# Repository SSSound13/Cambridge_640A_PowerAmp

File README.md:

# Новая плата для любимого Cambridge 640A

> [!CAUTION]
> Версия сейчас находится на проверке.

Cambridge Audio Azur 640A хочется сохранить в работе. Этот проект посвящён восстановлению усилителя на новой четырёхслойной плате: с привычной схемотехникой, выходными модулями Sanken SAP15 и более удобным обслуживанием.

Плата разработана для **640A первой версии (V1)** на основе заводского узла AP12707/6 и PCB AP12708/6a. Можно использовать пригодные детали исходного усилителя, а схему, разводку и каждое изменение изучить в KiCad.

*Монтажный вид из KiCad, не фотография собранной платы. [Рассмотреть в деталях](doc/v2/preview/front-assembly.png).*

## Что даёт новая плата

### Сохранить знакомый усилитель

В основе остаётся схема Cambridge, включая выходные SAP15. Контур и крепёж взяты за основу из оригинальной конструкции, чтобы проект подходил для восстановления имеющегося аппарата. Перенос исправных компонентов позволяет сохранить значительную часть усилителя. При этом SAP15 сняты с производства, а фактическую посадку деталей и радиатора ещё нужно проверить.

### Меньше проводов, проще обслуживание

Соединения, которые раньше выполнялись перемычками и проводами, перенесены в медь четырёхслойной платы. Трансформатор и акустика подключаются через разъёмы JST: для снятия платы эти провода больше не нужно отпаивать. Отдельные контрольные точки облегчают подключение щупов при настройке тока покоя, а крупные подписи помогают ориентироваться при сборке.

### Свой путь для силовых и сигнальных токов

Выходной каскад потребляет большие токи, а вход работает с малым сигналом. Если они используют общие участки земли, падение напряжения на этих участках может влиять на сигнал.

В новой разводке силовая, сигнальная, цифровая и вспомогательная земли разделены и сведены к звезде. Внутренние слои используются для питания и силовой земли. Цель: уменьшить взаимное влияние цепей и сделать пути токов понятными. Реальный результат по шуму и устойчивости предстоит измерить.

### Изменения с понятной причиной

В питании входных каскадов применены огнестойкие резисторы большей мощности, в основном выпрямителе выбраны диоды с большим запасом по току. Добавлены резисторы, ограничивающие рост сопротивления цепи регулировки тока покоя, и RC-снабберы для подавления звона вторичной обмотки.

На входе используются плёночные конденсаторы, увеличена ёмкость конденсаторов обратной связи. У каждой замены есть конкретная задача. Итоговую АЧХ, нагрев и поведение при неисправностях ещё нужно проверить; обещаний улучшенного звука без измерений здесь нет.

### Исходники, которые можно изучить и доработать

Схема, плата, специальные библиотеки и перечень компонентов доступны в репозитории. Можно проследить соединения, подобрать детали и понять причины изменений. В BOM указаны партномера и замечания по монтажу, рядом сохранены изображения и результаты проверок. Проект полезен и для собственного ремонта, и для обсуждения решений с другими разработчиками.

## Сравнение с оригиналом

Что меняется при переходе с заводской платы на новую. Номиналы и конструкция относятся к **актуальным исходникам v2**, а не старому производственному архиву. Три строки с отметкой ¹ содержат прежние расчётные оценки, ещё не перепроверенные для текущей v2. Результаты работы собранного усилителя предстоит измерить.

| Параметр | Оригинал AP12708/6a | Новая плата v2 |
|---|---|---|
| Слои меди | Один снизу, соединения сверху перемычками | Четыре; в проекте 70 мкм снаружи и 35 мкм внутри, номинальная толщина платы 1,6 мм |
| Перемычки | 19 LK по схеме и 5 проволочных WIRE LINK | Соединения выполнены медью платы; впаивать перемычки не нужно |
| Провода трансформатора и акустики | Впаяны в клеммы | Разъёмы JST VH 3,96 мм для силовых цепей и XH 2,5 мм для вспомогательной обмотки; J4 для корпуса сохранена |
| Питание ±45 В выходных каскадов | Дорожки и отрезки провода | Полигоны In1.Cu, шины батареи конденсаторов шириной 3,4 мм |
| Силовая земля | Дорожки и провода WIRE1–4 к звезде | Полигон PGND на отдельном внутреннем слое In2.Cu |
| Разделение земель | Провода и общие участки дорожек | PGND / GND / digital / AUX0V, соединение в звезде NT1–NT3 |
| Влияние токов фильтров на опору входа, мВ/А (L / R)¹ | 11,5 / 21,8 | 0,15 / 0,15 |
| Влияние тока заряда и выпрямителя на опору входа, мВ/А¹ | 0,03–0,05 | 0 в прежней модели |
| Перекрёстная связь возвратов АС L↔R, мВ/А¹ | 0,008 | 0,0002 |
| Мост основного питания D17–D20 | 1N5402, 3 А | Diotec BY550-400, 5 А / 400 В, по текущему BOM |
| Снабберы вторичной обмотки | Нет | 47 Ом + 100 нФ на каждую половину; сопротивление подбирается по измеренному звону |
| Регулировка тока покоя R116 / R68 | Реостат 47 Ом | Добавлены параллельные 100 Ом R120 / R121; исправная цепь до ≈32 Ом² |
| Контроль тока покоя | Щупы на выводах резисторов 0,22 Ом | Отдельные контрольные точки TP1–TP6 |
| R41, R43, R96, R98 | 150 Ом / 0,25 Вт | 150 Ом / 0,5 Вт, огнестойкие |
| Входной конденсатор C18 / C39 | 10 мкФ, неполярный электролит | 2,2 мкФ, плёнка WIMA MKS2 |
| Конденсатор обратной связи C17 / C41 | 100 мкФ NP; расчётный полюс RC ≈1,6 Гц³ | 220 мкФ NP; расчётный полюс RC ≈0,7 Гц³ |
| Цепь Цобеля C24 / C28 | 100 нФ и 4,7 Ом / 3 Вт | 100 нФ / 250 В MKT; резисторы 4,7 Ом / 3 Вт остаются проволочными |
| +5 В для PIC | 7805 на общем радиаторе с 7815 / 7915 | Возвращён штатный 7805 на общем радиаторе, стандартный KiCad TO-220; TRACO не используется, C81 удалён |
| Электрическая связь радиатора стабилизаторов | Через фланец 7805 | Через фланец U8 (digital); отдельная дорожка H8 удалена. U9 и U10 устанавливаются с изоляторами |
| Выходные модули | Sanken SAP15N / SAP15P | Те же типы модулей, монтаж на радиаторе; фактическая посадка проверяется при сборке |
| Топология усилителя и защиты | Схемотехника Cambridge 640A V1 | Базовая схема сохранена; доработаны вспомогательные цепи, компоненты и разводка |

¹ **Исторические расчётные оценки, не результаты измерений.** Эти три строки восстановлены из [прежнего сравнения и расчёта сопротивлений земли от 25.09.2026](https://github.com/SSSound13/Cambridge_640A_PowerAmp/blob/8188b4cc4bade1c1e03b41d10146da4cc2be14a8/README.md). Расчёт не повторён для текущей исправленной v2. Ноль в резистивной модели не означает отсутствия реальных помех, а эти числа не являются измерением шума или разделения каналов усилителя.

² 47 Ом ∥ 100 Ом ≈ 32 Ом по номиналам компонентов. Это не гарантия безопасного тока покоя при любой неисправности; поведение требует проверки.

³ Оценка отдельной RC-цепи при 1 кОм: 1 / (2πRC). Это не измеренная нижняя граница АЧХ всего усилителя.

Полные типы деталей и монтажные ограничения: [BOM](BOM.md). Текущие исправления и проверки: [описание v2](doc/v2/MINIMAL_FIXES.md) и [результаты проверок](doc/v2/VALIDATION.md).

## Версия 2: что уже сделано и что дальше

После первой изготовленной партии подготовлены минимальные исправления v2:

- Устранено ошибочное соединение входа U6 с +15 V.
- Возвращён стабилизатор 7805, убраны C81 и отдельная дорожка H8 для установки целого радиатора.
- Укрупнены и упорядочены подписи, добавлены обозначения контрольных точек, контур радиатора и ссылка на проект. QR расположен сверху под H2, над R71; полный URL текстом сохранён снизу.

Остальные компоненты сохранены на своих местах. Проверки файлов выполнены, но работа собранной платы, защита, механика и тепловой режим ещё не подтверждены. Подробности: [исправления и монтаж](doc/v2/MINIMAL_FIXES.md), [результаты и границы проверок](doc/v2/VALIDATION.md).

**Gerber обновлены 07.11.2026:** [текущий комплект](gerber/) и [ZIP](640A_PowerAmp_v2_fab_2026-11-07.zip) обновлены после смещения R12 на 0,8 мм вниз от C7; четыре остальных пересечения приняты в исключения. Исправление U6 сохранено. Проверка: 0 ошибок, 0 активных предупреждений, 0 неразведённых соединений и расхождений со схемой. [Состав, настройки и результаты проверки](gerber/README.md). **ZIP от 03.10.2026 остаётся только историческим архивом: в нём ошибочная связь U6 с +15 V, использовать его для нового заказа нельзя.** Обновление файлов не исправляет уже изготовленную плату.

В [отдельном плане v3](https://github.com/SSSound13/Cambridge_640A_PowerAmp/blob/v3/TODO.md) находятся симметричная компоновка каналов и дальнейшее улучшение размещения компонентов.

## С чего начать

- **Посмотреть плату:** [монтажный вид и шелкография](doc/v2/preview/).
- **Разобраться с деталями:** [BOM и замечания по сборке](BOM.md).
- **Открыть исходники:** [проект KiCad](640A_PowerAmp.kicad_pro), нужен KiCad 10.0 или новее.
- **Проверить текущий статус:** [исправления v2](doc/v2/MINIMAL_FIXES.md) и [проверки](doc/v2/VALIDATION.md). Старые отчёты и сборочные PDF оставлены для истории.

Здесь **V1 означает поколение усилителя**, а **v2 означает версию новой платы**. Совместимость с Cambridge 640A V2 не заявляется.

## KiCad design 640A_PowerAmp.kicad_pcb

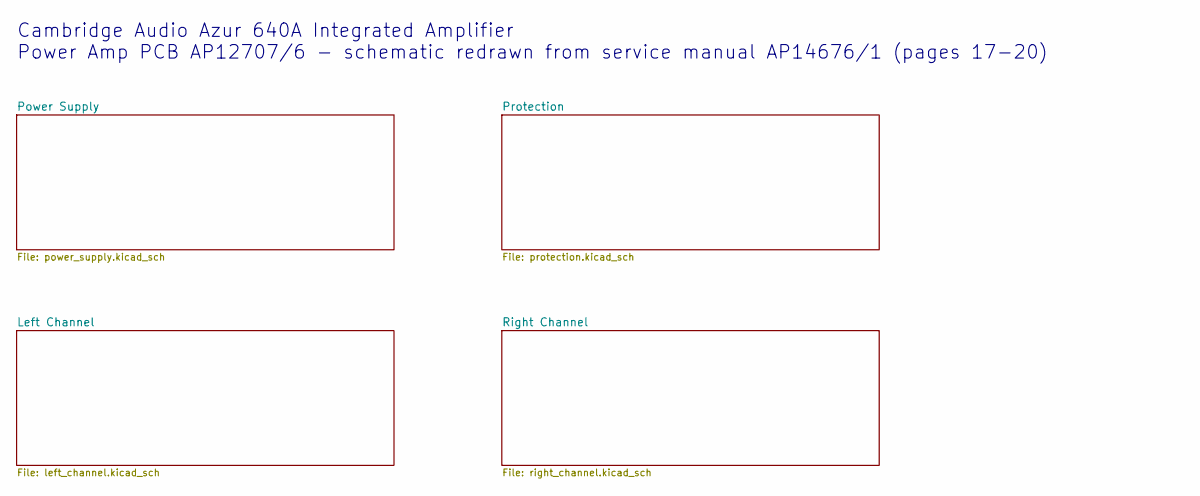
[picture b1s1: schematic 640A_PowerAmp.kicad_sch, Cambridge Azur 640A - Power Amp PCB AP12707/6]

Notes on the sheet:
Cambridge Audio Azur 640A Integrated Amplifier Power Amp PCB AP12707/6 - schematic redrawn from service manual AP14676/1 (pages 17-20)

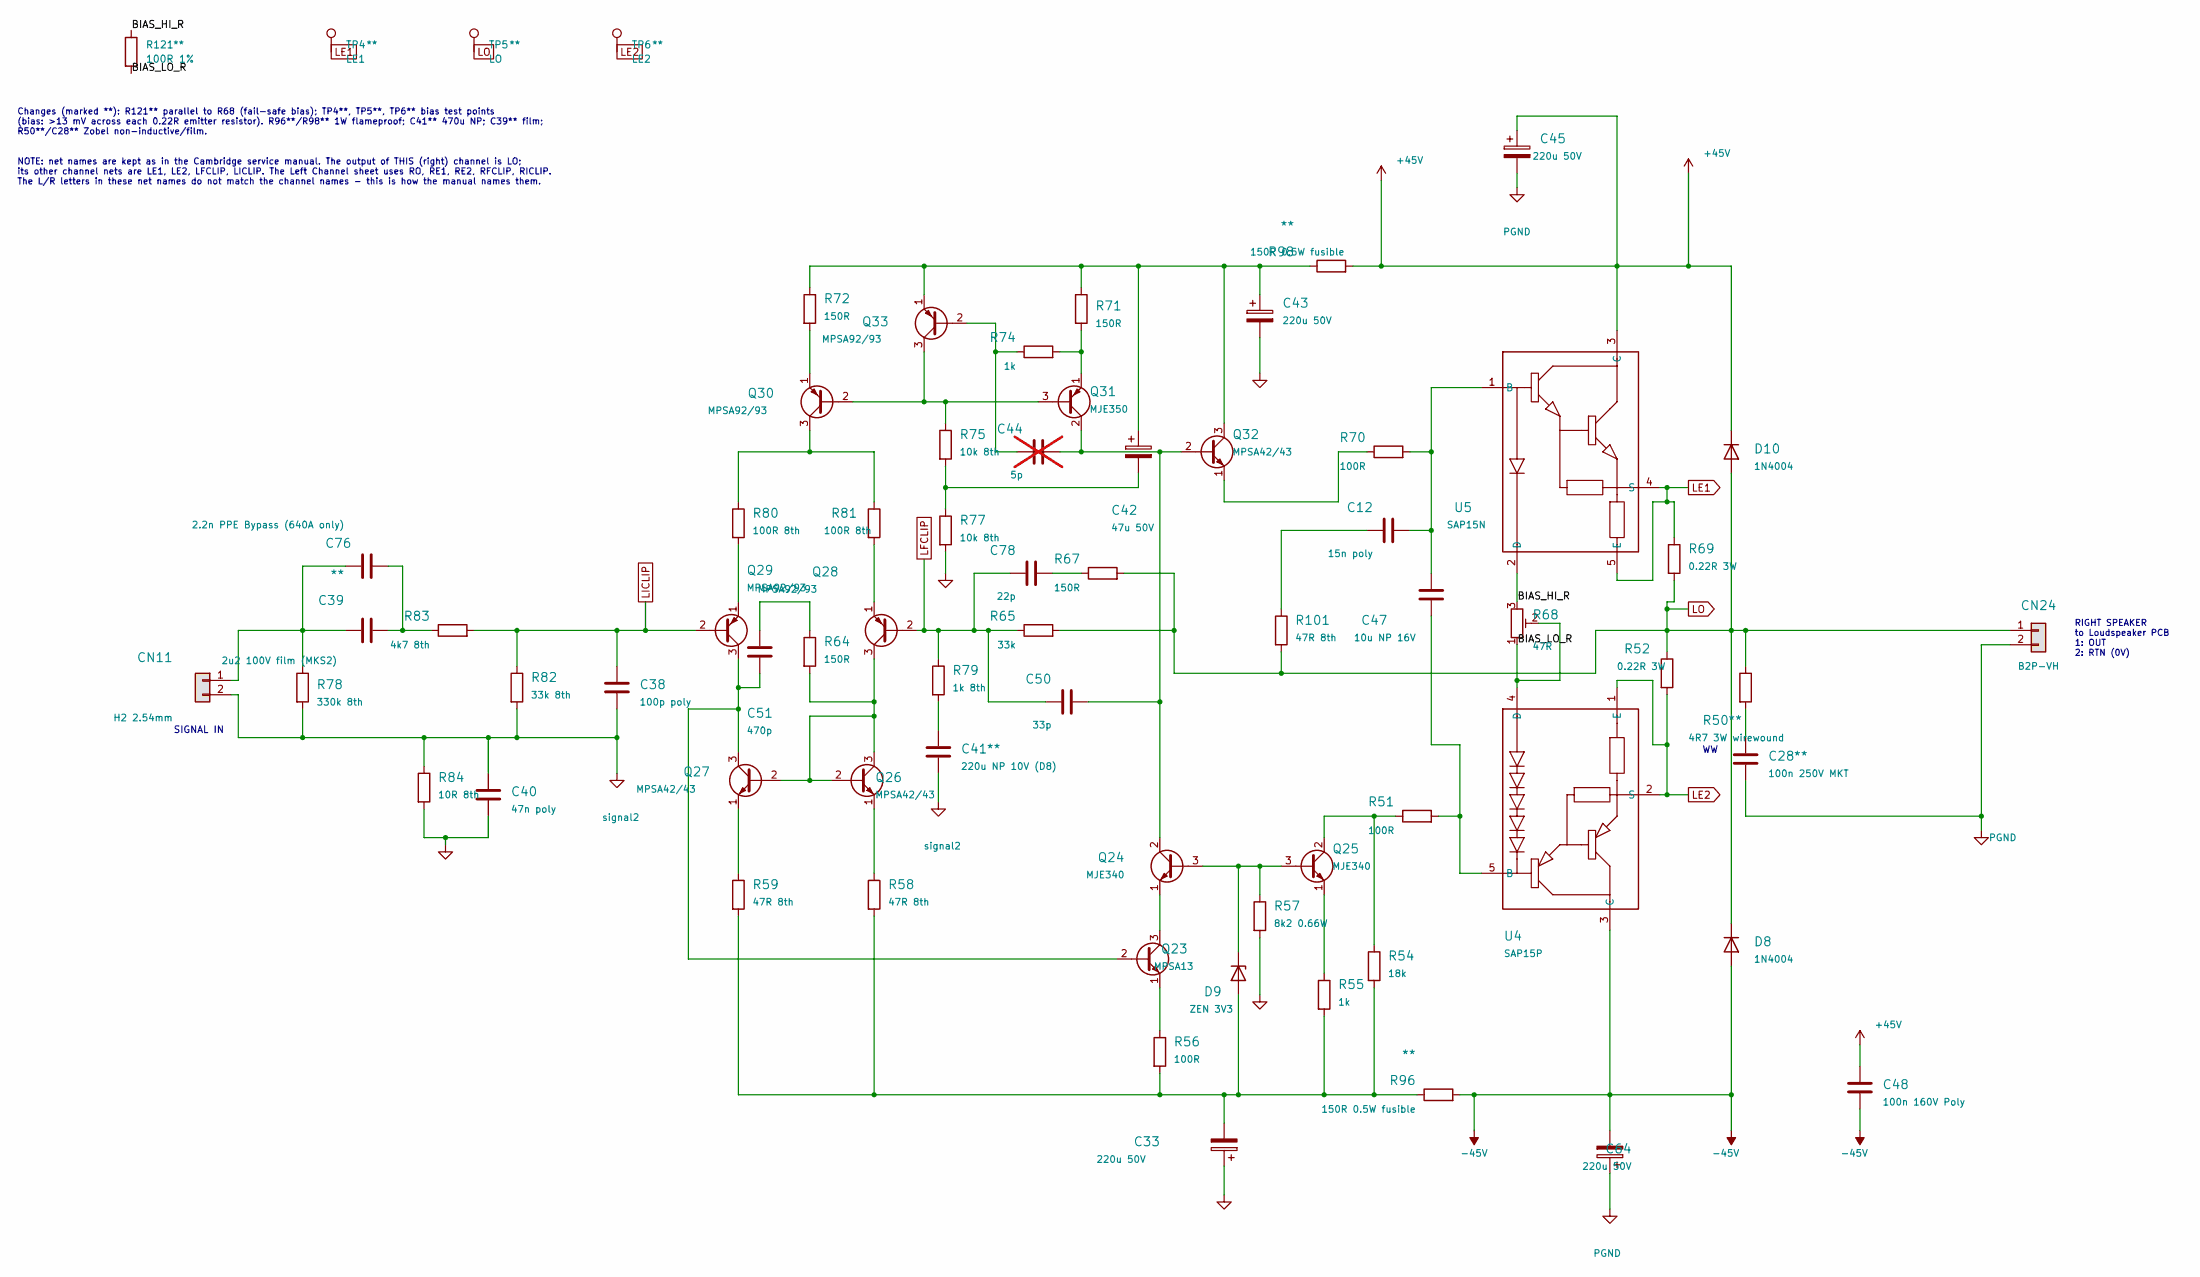
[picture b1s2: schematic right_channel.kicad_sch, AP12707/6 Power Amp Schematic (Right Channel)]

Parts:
C12: 15n poly; C_Rect_L7.2mm_W2.5mm_P5.00mm_FKS2_FKP2_MKS2_MKP2
C28: 100n 250V MKT; C_Rect_L9.0mm_W3.2mm_P7.50mm_MKT; MPN B32560J3104K000
C33, C43, C45, C64: 220u 50V; CP_Radial_D10.0mm_P5.00mm
C38: 100p poly; C_Rect_L7.2mm_W2.5mm_P5.00mm_FKS2_FKP2_MKS2_MKP2
C39: 2u2 100V film (MKS2); C_Rect_L7.2mm_W11.0mm_P5.00mm_FKS2_FKP2_MKS2_MKP2; MPN MKS2D042201N00KO00 (MKS2-2.2U/100-R)
C40: 47n poly; C_Rect_L7.2mm_W2.5mm_P5.00mm_FKS2_FKP2_MKS2_MKP2
C41: 220u NP 10V (D8); C_Radial_D8.0mm_H11.5mm_P3.50mm; MPN ECE-A1AN221U
C42: 47u 50V; CP_Radial_D6.3mm_P2.50mm
C44: 5p; C_Disc_D5.0mm_W2.5mm_P5.00mm; not fitted
C47: 10u NP 16V; C_Radial_D5.0mm_P5.00mm_NP
C48: 100n 160V Poly; C_Rect_L13.0mm_W4.0mm_P10.00mm_FKS3_FKP3_MKS4
C50: 33p; C_Rect_L7.2mm_W2.5mm_P5.00mm_FKS2_FKP2_MKS2_MKP2
C51: 470p; C_Disc_D5.0mm_W2.5mm_P5.00mm
C76: 2.2n PPE Bypass (640A only); C_Rect_L7.2mm_W2.5mm_P5.00mm_FKS2_FKP2_MKS2_MKP2
C78: 22p; C_Disc_D5.0mm_W2.5mm_P5.00mm
CN11: H2 2.54mm; JST_XH_B2B-XH-A_1x02_P2.50mm_Vertical
CN24: B2P-VH; JST_VH_B2P-VH_1x02_P3.96mm_Vertical; MPN B2P-VH
D8, D10: 1N4004; D_DO-41_SOD81_P8.89mm_Horizontal
D9: ZEN 3V3; D_DO-35_SOD27_P7.62mm_Horizontal
Q23: MPSA13; TO-92_Inline_Wide
Q24, Q25: MJE340; TO-126-3_Vertical
Q26, Q27, Q32: MPSA42/43; TO-92_Inline_Wide
Q28, Q29, Q30, Q33: MPSA92/93; TO-92_Inline_Wide
Q31: MJE350; TO-126-3_Vertical
R50: 4R7 3W wirewound; R_Axial_DIN0516_L15.5mm_D5.0mm_P18.42mm_Horizontal; MPN AC03000004708JAC00
R51, R56, R70: 100R; R_Axial_DIN0207_L6.3mm_D2.5mm_P10.16mm_Horizontal
R52, R69: 0.22R 3W; R_Axial_DIN0516_L15.5mm_D5.0mm_P19.69mm_Horizontal
R54: 18k; R_Axial_DIN0207_L6.3mm_D2.5mm_P10.16mm_Horizontal
R55, R74: 1k; R_Axial_DIN0207_L6.3mm_D2.5mm_P10.16mm_Horizontal
R57: 8k2 0.66W; R_Axial_DIN0309_L9.0mm_D3.2mm_P11.81mm_Horizontal
R58, R59: 47R 8th; R_Axial_DIN0204_L3.6mm_D1.6mm_P7.62mm_Horizontal
R64, R67: 150R; R_Axial_DIN0204_L3.6mm_D1.6mm_P7.62mm_Horizontal
R65: 33k; R_Axial_DIN0207_L6.3mm_D2.5mm_P10.16mm_Horizontal
R68: 47R; Potentiometer_Bourns_3296W_Vertical
R71, R72: 150R; R_Axial_DIN0207_L6.3mm_D2.5mm_P10.16mm_Horizontal
R75, R77: 10k 8th; R_Axial_DIN0204_L3.6mm_D1.6mm_P7.62mm_Horizontal
R78: 330k 8th; R_Axial_DIN0204_L3.6mm_D1.6mm_P7.62mm_Horizontal
R79: 1k 8th; R_Axial_DIN0204_L3.6mm_D1.6mm_P7.62mm_Horizontal
R80, R81: 100R 8th; R_Axial_DIN0204_L3.6mm_D1.6mm_P7.62mm_Horizontal
R82: 33k 8th; R_Axial_DIN0204_L3.6mm_D1.6mm_P7.62mm_Horizontal
R83: 4k7 8th; R_Axial_DIN0204_L3.6mm_D1.6mm_P7.62mm_Horizontal
R84: 10R 8th; R_Axial_DIN0204_L3.6mm_D1.6mm_P7.62mm_Horizontal
R96, R98: 150R 0.5W fusible; R_Axial_DIN0207_L6.3mm_D2.5mm_P10.16mm_Horizontal; MPN FRN50J150R/S
R101: 47R 8th; R_Axial_DIN0204_L3.6mm_D1.6mm_P5.08mm_Horizontal
R121: 100R 1%; R_Axial_DIN0204_L3.6mm_D1.6mm_P2.54mm_Vertical; MPN MF-25 0.25W 100R 1%
TP4: LE1; TestPoint_THTPad_D2.0mm_Drill1.0mm
TP5: LO; TestPoint_THTPad_D2.0mm_Drill1.0mm
TP6: LE2; TestPoint_THTPad_D2.0mm_Drill1.0mm
U4: SAP15P; TO-3P-5_SAP15_Horizontal
U5: SAP15N; TO-3P-5_SAP15_Horizontal

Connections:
+45V: C45.1, C48.1, D10.1 (K), R98.2, U5.3 (C); also elsewhere on the board
-45V: C48.2, C64.2, D8.2 (A), R96.2, U4.3 (C); also elsewhere on the board
/Right Channel/BIAS_HI_R: R68.3, R121.1, U5.2 (D)
/Right Channel/BIAS_LO_R: R68.1, R68.2, R121.2, U4.4 (D)
GND: C33.1, C40.2, C43.2, R57.2, R77.2, R84.2; also elsewhere on the board
LE1: R69.1, TP4.1 (1_1), U5.4 (S), U5.5 (E); also elsewhere on the board
LE2: R52.2, TP6.1 (1_1), U4.1 (E), U4.2 (S); also elsewhere on the board
LFCLIP: C50.1, C78.1, Q28.2 (B), R65.1, R79.1; also elsewhere on the board
LICLIP: C38.1, Q29.2 (B), R82.1, R83.2; also elsewhere on the board
LO: CN24.1, D8.1 (K), D10.2 (A), R50.1, R52.1, R65.2, R67.2, R69.2, R101.2, TP5.1 (1_1); also elsewhere on the board
unnamed: C12.1, R101.1
unnamed: C28.1, R50.2
unnamed: C39.2, C76.2, R83.1
unnamed: C41.1, R79.2
unnamed: C42.2, R75.2, R77.1
unnamed: C51.1, R64.1
unnamed: C78.2, R67.1
unnamed: C39.1, C76.1, CN11.1, R78.1
unnamed: C33.2, D9.2 (A), R54.2, R55.2, R56.2, R58.2, R59.2, R96.1
unnamed: D9.1 (K), Q24.3 (B), Q25.3 (B), R57.1
unnamed: C51.2, Q23.2 (B), Q27.3 (C), Q29.3 (C)
unnamed: Q23.3 (C), Q24.1 (E)
unnamed: Q23.1 (E), R56.1
unnamed: C44.2, C50.2, Q24.2 (C), Q31.2 (C), Q32.2 (B)
unnamed: Q25.2 (C), R51.1, R54.1
unnamed: Q25.1 (E), R55.1
unnamed: Q26.2 (B), Q26.3 (C), Q27.2 (B), Q28.3 (C), R64.2
unnamed: Q26.1 (E), R58.1
unnamed: Q27.1 (E), R59.1
unnamed: Q28.1 (E), R81.2
unnamed: Q29.1 (E), R80.2
unnamed: Q30.2 (B), Q31.3 (B), Q33.3 (C), R75.1
unnamed: Q30.3 (C), R80.1, R81.1
unnamed: Q30.1 (E), R72.2
unnamed: Q31.1 (E), R71.2, R74.2
unnamed: C42.1, C43.1, Q32.3 (C), Q33.1 (E), R71.1, R72.1, R98.1
unnamed: Q32.1 (E), R70.1
unnamed: C44.1, Q33.2 (B), R74.1
unnamed: C47.2, R51.2, U4.5 (B)
unnamed: C12.2, C47.1, R70.2, U5.1 (B)
PGND: C28.2, C45.2, C64.1, CN24.2; also elsewhere on the board
signal2: C38.2, C40.1, C41.2, CN11.2, R78.2, R82.2, R84.1

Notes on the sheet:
RIGHT SPEAKER to Loudspeaker PCB 1: OUT 2: RTN (0V)
NOTE: net names are kept as in the Cambridge service manual. The output of THIS (right) channel is LO; its other channel nets are LE1, LE2, LFCLIP, LICLIP. The Left Channel sheet uses RO, RE1, RE2, RFCLIP, RICLIP. The L/R letters in these net names do not match the channel names - this is how the m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
SIGNAL IN
Changes (marked **): R121** parallel to R68 (fail-safe bias); TP4**, TP5**, TP6** bias test points (bias: >13 mV across each 0.22R emitter resistor). R96**/R98** 1W flameproof; C41** 470u NP; C39** film; R50**/C28** Zobel non-inductive/film.

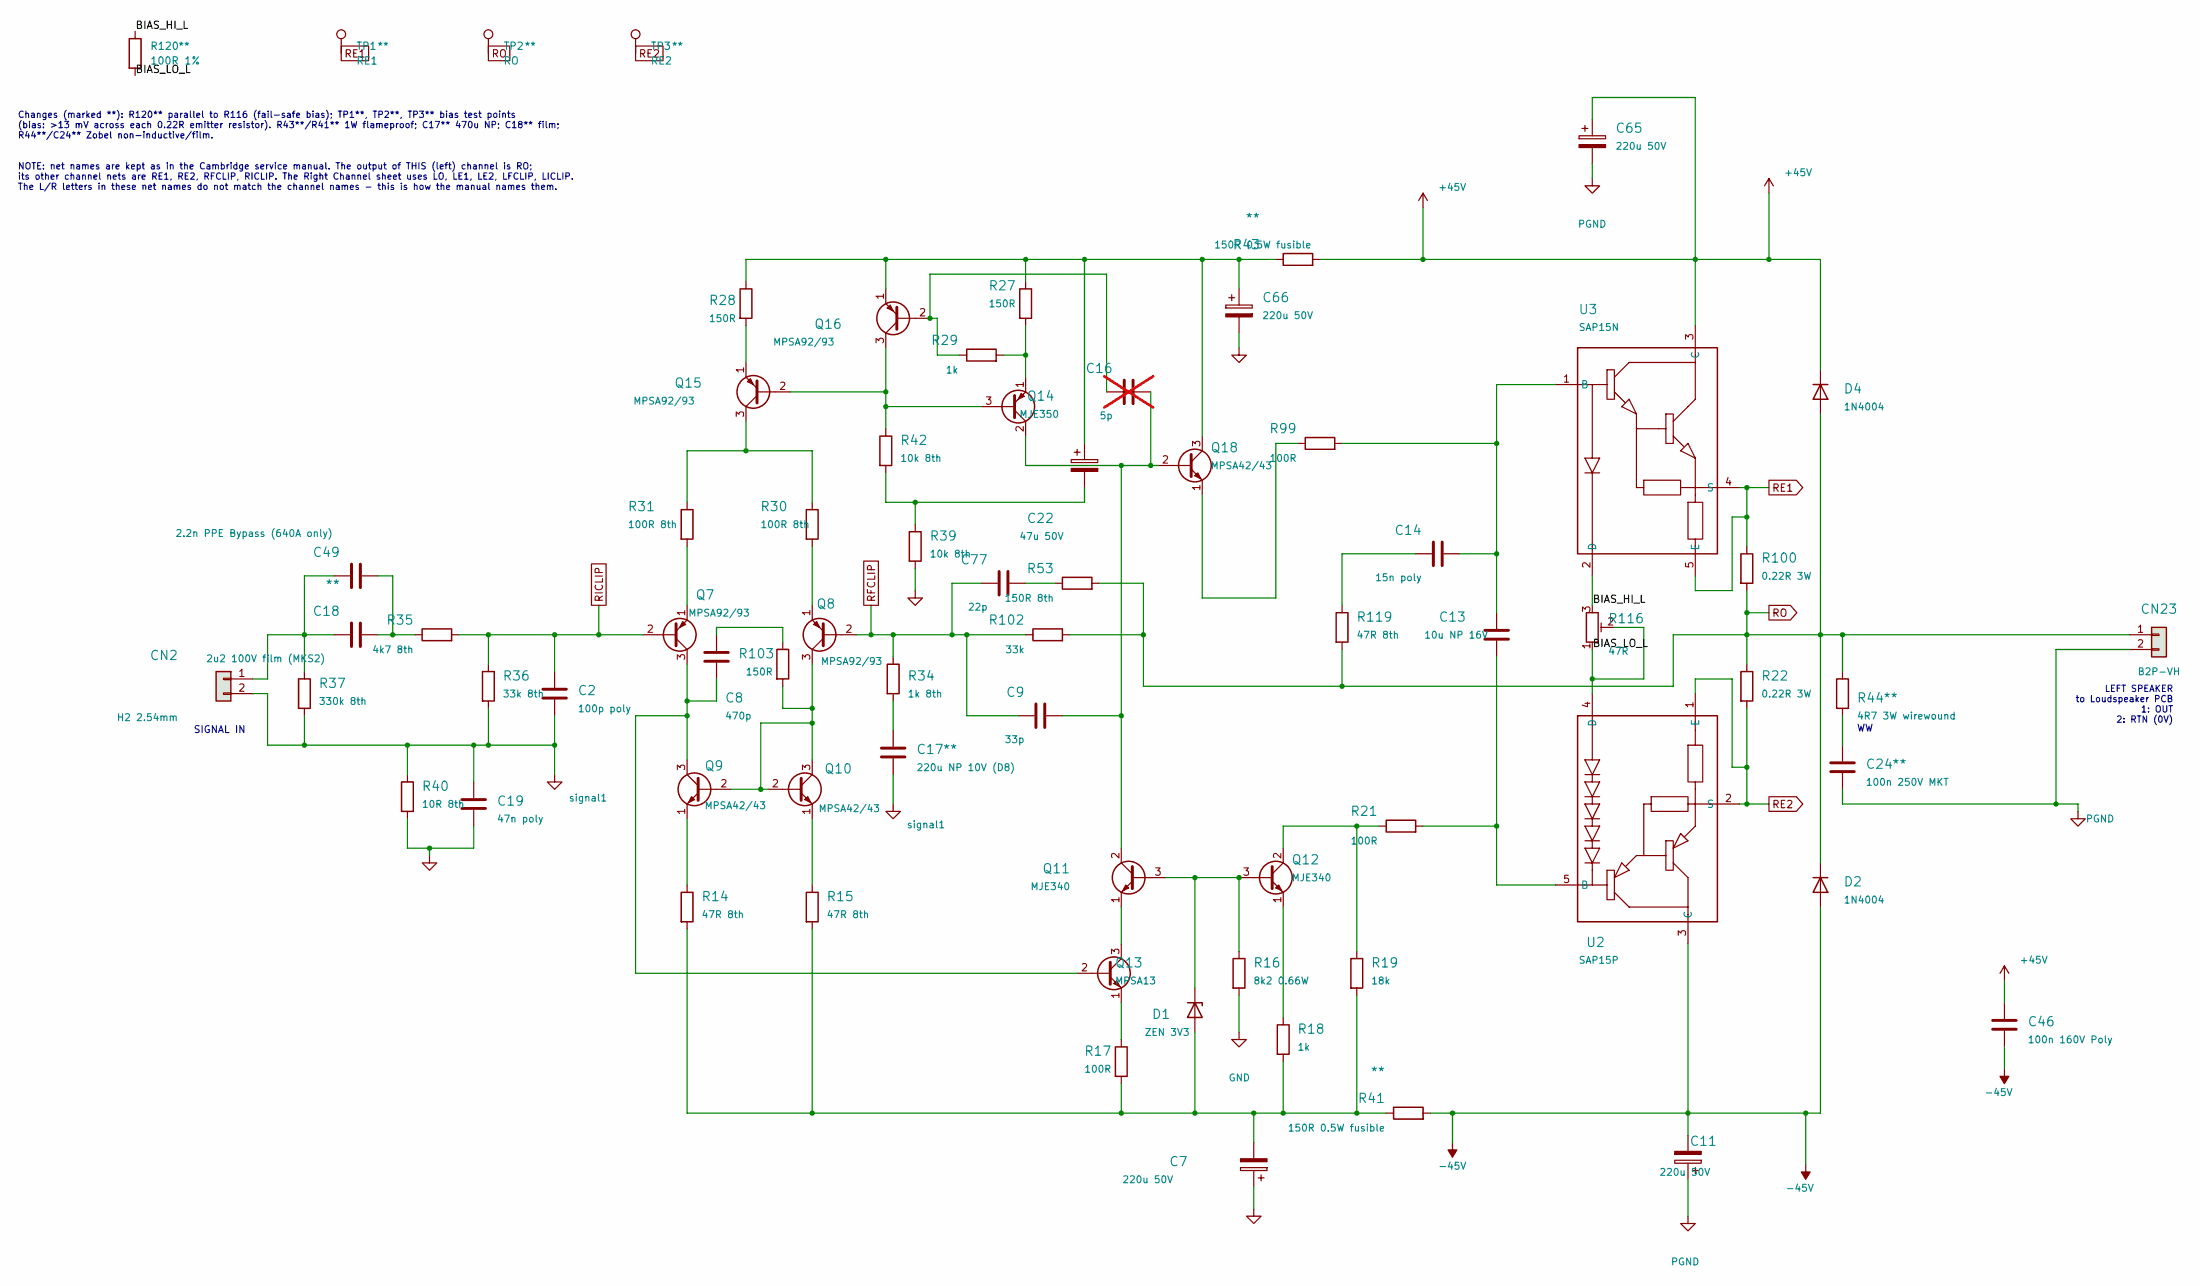
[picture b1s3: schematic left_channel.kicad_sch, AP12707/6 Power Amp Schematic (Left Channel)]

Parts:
C2: 100p poly; C_Rect_L7.2mm_W2.5mm_P5.00mm_FKS2_FKP2_MKS2_MKP2
C7, C11, C65, C66: 220u 50V; CP_Radial_D10.0mm_P5.00mm
C8: 470p; C_Disc_D5.0mm_W2.5mm_P5.00mm
C9: 33p; C_Rect_L7.2mm_W2.5mm_P5.00mm_FKS2_FKP2_MKS2_MKP2
C13: 10u NP 16V; C_Radial_D5.0mm_P5.00mm_NP
C14: 15n poly; C_Rect_L7.2mm_W2.5mm_P5.00mm_FKS2_FKP2_MKS2_MKP2
C16: 5p; C_Disc_D5.0mm_W2.5mm_P5.00mm; not fitted
C17: 220u NP 10V (D8); C_Radial_D8.0mm_H11.5mm_P3.50mm; MPN ECE-A1AN221U
C18: 2u2 100V film (MKS2); C_Rect_L7.2mm_W11.0mm_P5.00mm_FKS2_FKP2_MKS2_MKP2; MPN MKS2D042201N00KO00 (MKS2-2.2U/100-R)
C19: 47n poly; C_Rect_L7.2mm_W2.5mm_P5.00mm_FKS2_FKP2_MKS2_MKP2
C22: 47u 50V; CP_Radial_D6.3mm_P2.50mm
C24: 100n 250V MKT; C_Rect_L9.0mm_W3.2mm_P7.50mm_MKT; MPN B32560J3104K000
C46: 100n 160V Poly; C_Rect_L13.0mm_W4.0mm_P10.00mm_FKS3_FKP3_MKS4
C49: 2.2n PPE Bypass (640A only); C_Rect_L7.2mm_W2.5mm_P5.00mm_FKS2_FKP2_MKS2_MKP2
C77: 22p; C_Disc_D5.0mm_W2.5mm_P5.00mm
CN2: H2 2.54mm; JST_XH_B2B-XH-A_1x02_P2.50mm_Vertical
CN23: B2P-VH; JST_VH_B2P-VH_1x02_P3.96mm_Vertical; MPN B2P-VH
D1: ZEN 3V3; D_DO-35_SOD27_P7.62mm_Horizontal
D2, D4: 1N4004; D_DO-41_SOD81_P8.89mm_Horizontal
Q7, Q8, Q15, Q16: MPSA92/93; TO-92_Inline_Wide
Q9, Q10, Q18: MPSA42/43; TO-92_Inline_Wide
Q11, Q12: MJE340; TO-126-3_Vertical
Q13: MPSA13; TO-92_Inline_Wide
Q14: MJE350; TO-126-3_Vertical
R14, R15: 47R 8th; R_Axial_DIN0204_L3.6mm_D1.6mm_P7.62mm_Horizontal
R16: 8k2 0.66W; R_Axial_DIN0309_L9.0mm_D3.2mm_P11.81mm_Horizontal
R17, R21, R99: 100R; R_Axial_DIN0207_L6.3mm_D2.5mm_P10.16mm_Horizontal
R18, R29: 1k; R_Axial_DIN0207_L6.3mm_D2.5mm_P10.16mm_Horizontal
R19: 18k; R_Axial_DIN0207_L6.3mm_D2.5mm_P10.16mm_Horizontal
R22, R100: 0.22R 3W; R_Axial_DIN0516_L15.5mm_D5.0mm_P19.69mm_Horizontal
R27, R28: 150R; R_Axial_DIN0207_L6.3mm_D2.5mm_P10.16mm_Horizontal
R30, R31: 100R 8th; R_Axial_DIN0204_L3.6mm_D1.6mm_P7.62mm_Horizontal
R34: 1k 8th; R_Axial_DIN0204_L3.6mm_D1.6mm_P7.62mm_Horizontal
R35: 4k7 8th; R_Axial_DIN0204_L3.6mm_D1.6mm_P7.62mm_Horizontal
R36: 33k 8th; R_Axial_DIN0204_L3.6mm_D1.6mm_P7.62mm_Horizontal
R37: 330k 8th; R_Axial_DIN0204_L3.6mm_D1.6mm_P7.62mm_Horizontal
R39, R42: 10k 8th; R_Axial_DIN0204_L3.6mm_D1.6mm_P7.62mm_Horizontal
R40: 10R 8th; R_Axial_DIN0204_L3.6mm_D1.6mm_P7.62mm_Horizontal
R41, R43: 150R 0.5W fusible; R_Axial_DIN0207_L6.3mm_D2.5mm_P10.16mm_Horizontal; MPN FRN50J150R/S
R44: 4R7 3W wirewound; R_Axial_DIN0516_L15.5mm_D5.0mm_P18.42mm_Horizontal; MPN AC03000004708JAC00
R53: 150R 8th; R_Axial_DIN0204_L3.6mm_D1.6mm_P7.62mm_Horizontal
R102: 33k; R_Axial_DIN0207_L6.3mm_D2.5mm_P10.16mm_Horizontal
R103: 150R; R_Axial_DIN0204_L3.6mm_D1.6mm_P7.62mm_Horizontal
R116: 47R; Potentiometer_Bourns_3296W_Vertical
R119: 47R 8th; R_Axial_DIN0204_L3.6mm_D1.6mm_P5.08mm_Horizontal
R120: 100R 1%; R_Axial_DIN0204_L3.6mm_D1.6mm_P2.54mm_Vertical; MPN MF-25 0.25W 100R 1%
TP1: RE1; TestPoint_THTPad_D2.0mm_Drill1.0mm
TP2: RO; TestPoint_THTPad_D2.0mm_Drill1.0mm
TP3: RE2; TestPoint_THTPad_D2.0mm_Drill1.0mm
U2: SAP15P; TO-3P-5_SAP15_Horizontal
U3: SAP15N; TO-3P-5_SAP15_Horizontal

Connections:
+45V: C46.1, C65.1, D4.1 (K), R43.2, U3.3 (C); also elsewhere on the board
-45V: C11.2, C46.2, D2.2 (A), R41.2, U2.3 (C); also elsewhere on the board
/Left Channel/BIAS_HI_L: R116.3, R120.1, U3.2 (D)
/Left Channel/BIAS_LO_L: R116.1, R116.2, R120.2, U2.4 (D)
GND: C7.1, C19.2, C66.2, R16.2, R39.2, R40.2; also elsewhere on the board
unnamed: C8.1, R103.1
unnamed: C14.1, R119.1
unnamed: C17.1, R34.2
unnamed: C18.2, C49.2, R35.1
unnamed: C22.2, R39.1, R42.2
unnamed: C24.1, R44.2
unnamed: C77.2, R53.1
unnamed: C18.1, C49.1, CN2.1, R37.1
unnamed: C7.2, D1.2 (A), R14.2, R15.2, R17.2, R18.2, R19.2, R41.1
unnamed: D1.1 (K), Q11.3 (B), Q12.3 (B), R16.1
unnamed: Q7.1 (E), R31.2
unnamed: Q8.1 (E), R30.2
unnamed: Q9.1 (E), R14.1
unnamed: Q8.3 (C), Q9.2 (B), Q10.2 (B), Q10.3 (C), R103.2
unnamed: Q10.1 (E), R15.1
unnamed: C9.2, C16.2, Q11.2 (C), Q14.2 (C), Q18.2 (B)
unnamed: Q11.1 (E), Q13.3 (C)
unnamed: Q12.2 (C), R19.1, R21.1
unnamed: Q12.1 (E), R18.1
unnamed: C8.2, Q7.3 (C), Q9.3 (C), Q13.2 (B)
unnamed: Q13.1 (E), R17.1
unnamed: Q14.3 (B), Q15.2 (B), Q16.3 (C), R42.1
unnamed: Q14.1 (E), R27.2, R29.2
unnamed: Q15.3 (C), R30.1, R31.1
unnamed: Q15.1 (E), R28.2
unnamed: C16.1, Q16.2 (B), R29.1
unnamed: C22.1, C66.1, Q16.1 (E), Q18.3 (C), R27.1, R28.1, R43.1
unnamed: Q18.1 (E), R99.1
unnamed: C13.2, R21.2, U2.5 (B)
unnamed: C13.1, C14.2, R99.2, U3.1 (B)
PGND: C11.1, C24.2, C65.2, CN23.2; also elsewhere on the board
RE1: R100.1, TP1.1 (1_1), U3.4 (S), U3.5 (E); also elsewhere on the board
RE2: R22.2, TP3.1 (1_1), U2.1 (E), U2.2 (S); also elsewhere on the board
RFCLIP: C9.1, C77.1, Q8.2 (B), R34.1, R102.1; also elsewhere on the board
RICLIP: C2.1, Q7.2 (B), R35.2, R36.1; also elsewhere on the board
RO: CN23.1, D2.1 (K), D4.2 (A), R22.1, R44.1, R53.2, R100.2, R102.2, R119.2, TP2.1 (1_1); also elsewhere on the board
signal1: C2.2, C17.2, C19.1, CN2.2, R36.2, R37.2, R40.1

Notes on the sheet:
NOTE: net names are kept as in the Cambridge service manual. The output of THIS (left) channel is RO; its other channel nets are RE1, RE2, RFCLIP, RICLIP. The Right Channel sheet uses LO, LE1, LE2, LFCLIP, LICLIP. The L/R letters in these net names do not match the channel names - this is how the m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
LEFT SPEAKER to Loudspeaker PCB 1: OUT 2: RTN (0V)
Changes (marked **): R120** parallel to R116 (fail-safe bias); TP1**, TP2**, TP3** bias test points (bias: >13 mV across each 0.22R emitter resistor). R43**/R41** 1W flameproof; C17** 470u NP; C18** film; R44**/C24** Zobel non-inductive/film.
SIGNAL IN

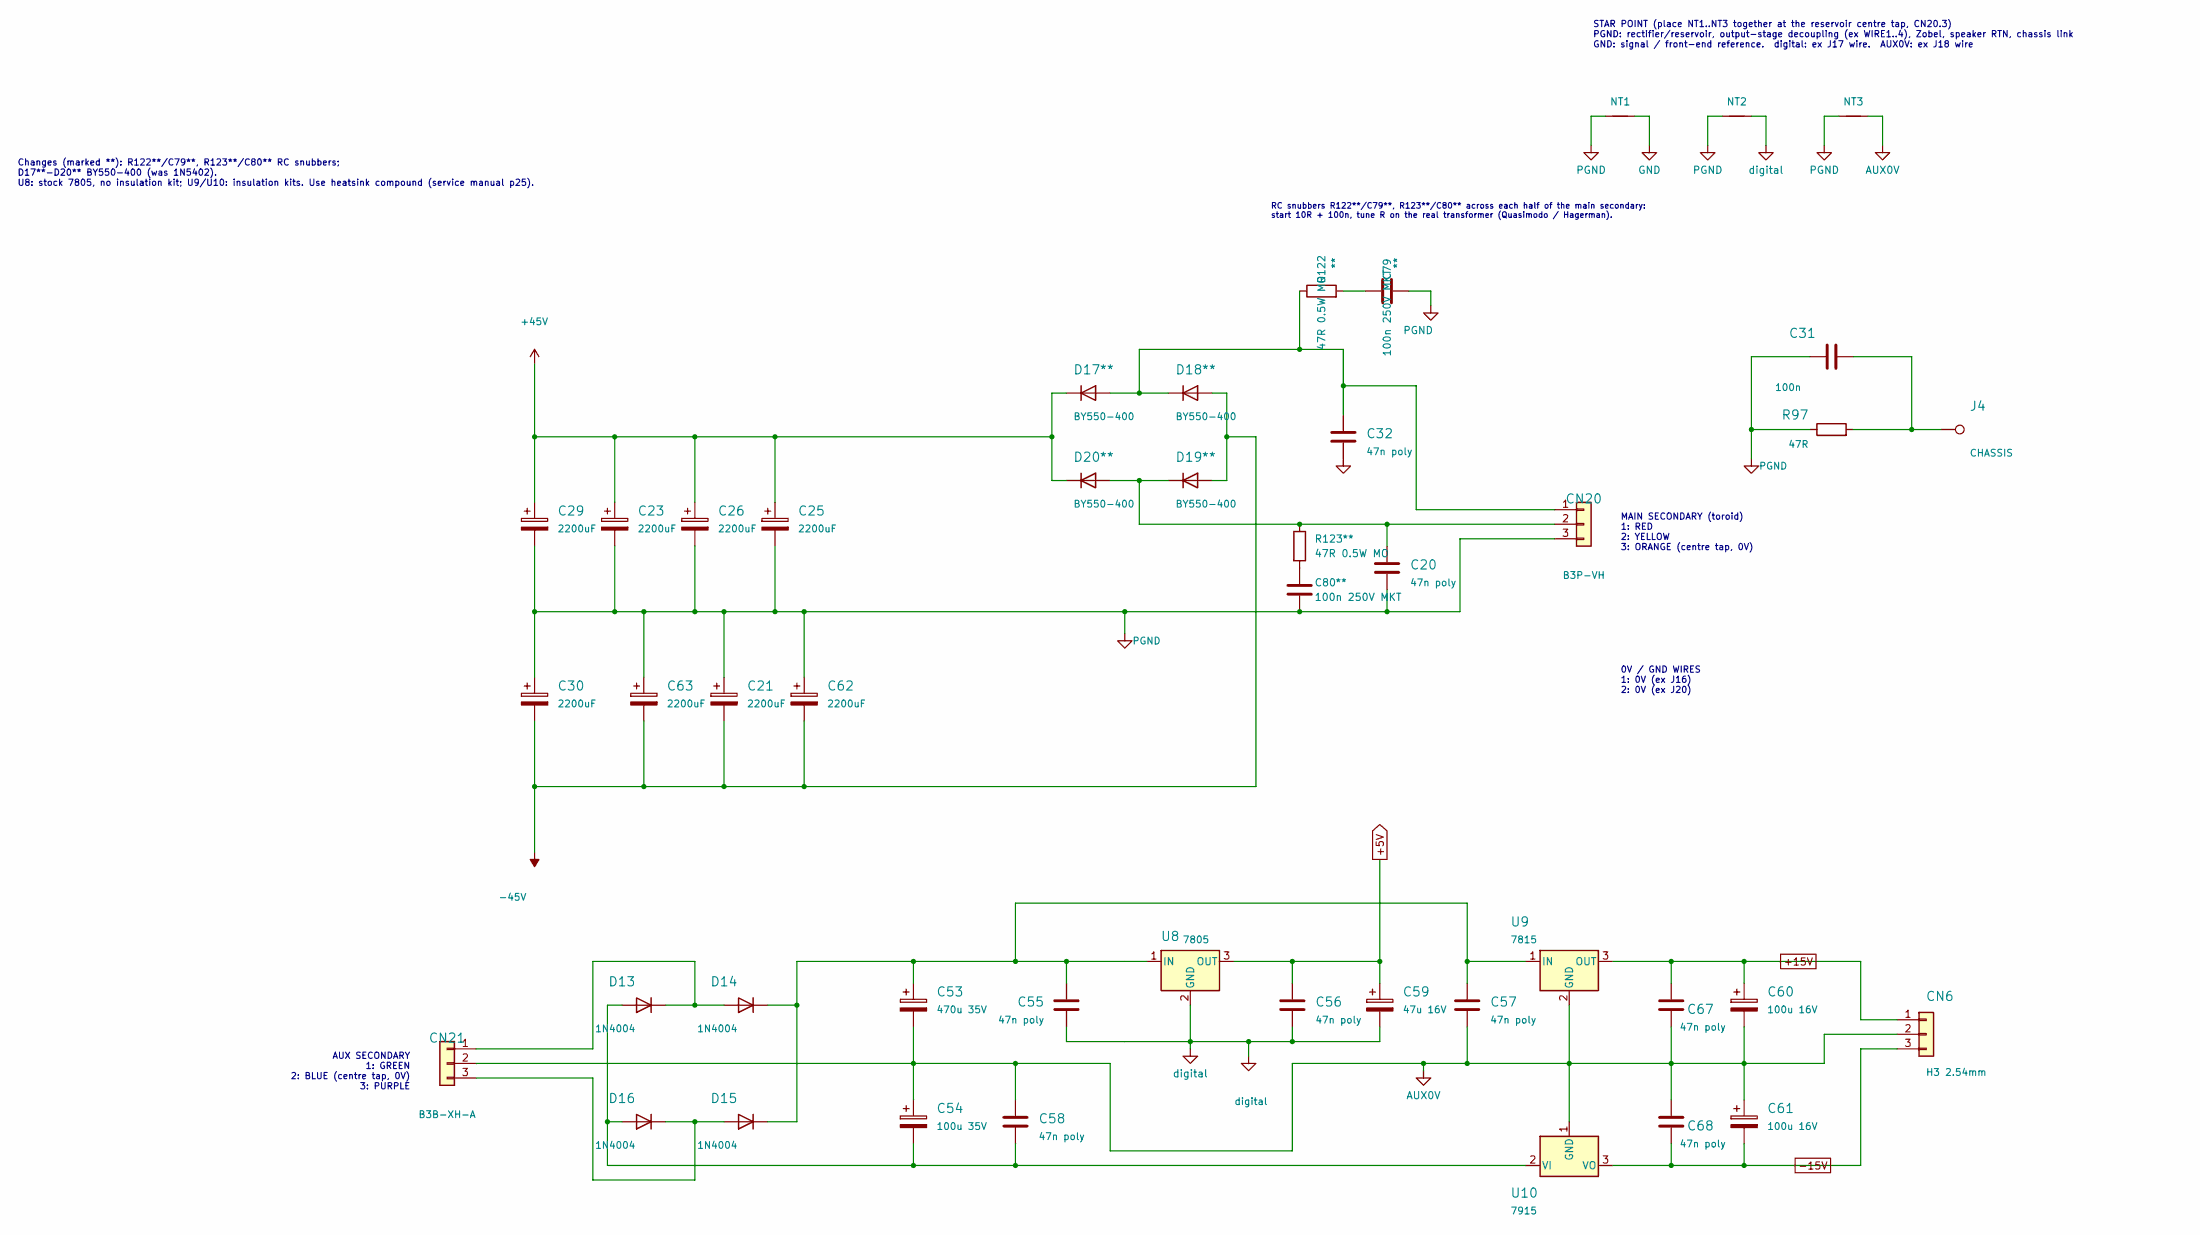
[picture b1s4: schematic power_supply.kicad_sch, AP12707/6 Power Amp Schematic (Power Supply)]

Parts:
C20, C32, C55, C56, C57, C58, C67, C68: 47n poly; C_Rect_L7.2mm_W2.5mm_P5.00mm_FKS2_FKP2_MKS2_MKP2
C21, C23, C25, C26, C29, C30, C62, C63: 2200uF; CP_Radial_D18.0mm_P7.50mm
C31: 100n; C_Disc_D7.5mm_W2.5mm_P5.00mm
C53: 470u 35V; CP_Radial_D10.0mm_P5.00mm
C54: 100u 35V; CP_Radial_D8.0mm_P3.50mm
C59: 47u 16V; CP_Radial_D5.0mm_P2.50mm
C60, C61: 100u 16V; CP_Radial_D5.0mm_P2.50mm
C79, C80: 100n 250V MKT; C_Rect_L9.0mm_W3.2mm_P7.50mm_MKT; MPN B32560J3104K000
CN6: H3 2.54mm; JST_XH_B3B-XH-A_1x03_P2.50mm_Vertical
CN20: B3P-VH; JST_VH_B3P-VH_1x03_P3.96mm_Vertical; MPN B3P-VH
CN21: B3B-XH-A; JST_XH_B3B-XH-A_1x03_P2.50mm_Vertical; MPN B3B-XH-A
D13, D14, D15, D16: 1N4004; D_DO-41_SOD81_P10.16mm_Horizontal
D17, D18, D19, D20: BY550-400; D_DO-201AD_P13.97mm_Horizontal; MPN BY550-400
J4: CHASSIS; TestPoint_THTPad_3.0x3.0mm_Drill1.5mm
NT1: NetTie_2; NetTie-2_THT_Star
NT2, NT3: NetTie_2; NetTie-2_THT_Pad1.0mm
R97: 47R; R_Axial_DIN0207_L6.3mm_D2.5mm_P10.16mm_Horizontal
R122, R123: 47R 0.5W MO; R_Axial_DIN0207_L6.3mm_D2.5mm_P2.54mm_Vertical; MPN MO-50 0.5W 47R 5%
U8: 7805; TO-220-3_Vertical
U9: 7815; TO-220-3_Vertical
U10: 7915; TO-220-3_Vertical

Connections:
+5V: C56.1, C59.1, U8.3 (OUT); also elsewhere on the board
+15V: C60.1, C67.1, CN6.1, U9.3 (OUT); also elsewhere on the board
+45V: C23.1, C25.1, C26.1, C29.1, D17.1 (K), D20.1 (K); also elsewhere on the board
-15V: C61.2, C68.2, CN6.3, U10.3 (VO); also elsewhere on the board
-45V: C21.2, C30.2, C62.2, C63.2, D18.2 (A), D19.2 (A); also elsewhere on the board
AUX0V: C53.2, C54.1, C57.2, C58.1, C60.2, C61.1, C67.2, C68.1, CN6.2, CN21.2, NT3.2, U9.2 (GND), U10.1 (GND)
GND: NT1.2; also elsewhere on the board
unnamed: C31.2, J4.1 (1_1), R97.2
unnamed: C79.1, R122.2
unnamed: C80.1, R123.2
unnamed: C32.1, CN20.1, D17.2 (A), D18.1 (K), R122.1
unnamed: C20.1, CN20.2, D19.1 (K), D20.2 (A), R123.1
unnamed: CN21.1, D13.1 (K), D14.2 (A)
unnamed: CN21.3, D15.2 (A), D16.1 (K)
unnamed: C54.2, C58.2, D13.2 (A), D16.2 (A), U10.2 (VI)
unnamed: C53.1, C55.1, C57.1, D14.1 (K), D15.1 (K), U8.1 (IN), U9.1 (IN)
PGND: C20.2, C21.1, C23.2, C25.2, C26.2, C29.2, C30.1, C31.1, C32.2, C62.1, C63.1, C79.2, C80.2, CN20.3, NT1.1, NT2.1, NT3.1, R97.1; also elsewhere on the board
digital: C55.2, C56.2, C59.2, NT2.2, U8.2 (GND); also elsewhere on the board

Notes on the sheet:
AUX SECONDARY 1: GREEN 2: BLUE (centre tap, 0V) 3: PURPLE
STAR POINT (place NT1..NT3 together at the reservoir centre tap, CN20.3) PGND: rectifier/reservoir, output-stage decoupling (ex WIRE1..4), Zobel, speaker RTN, chassis link GND: signal / front-end reference. digital: ex J17 wire. AUX0V: ex J18 wire
RC snubbers R122**/C79**, R123**/C80** across each half of the main secondary: start 10R + 100n, tune R on the real transformer (Quasimodo / Hagerman).
MAIN SECONDARY (toroid) 1: RED 2: YELLOW 3: ORANGE (centre tap, 0V)
0V / GND WIRES 1: 0V (ex J16) 2: 0V (ex J20)
Changes (marked **): R122**/C79**, R123**/C80** RC snubbers; D17**-D20** BY550-400 (was 1N5402). U8: stock 7805, no insulation kit; U9/U10: insulation kits. Use heatsink compound (service manual p25).
